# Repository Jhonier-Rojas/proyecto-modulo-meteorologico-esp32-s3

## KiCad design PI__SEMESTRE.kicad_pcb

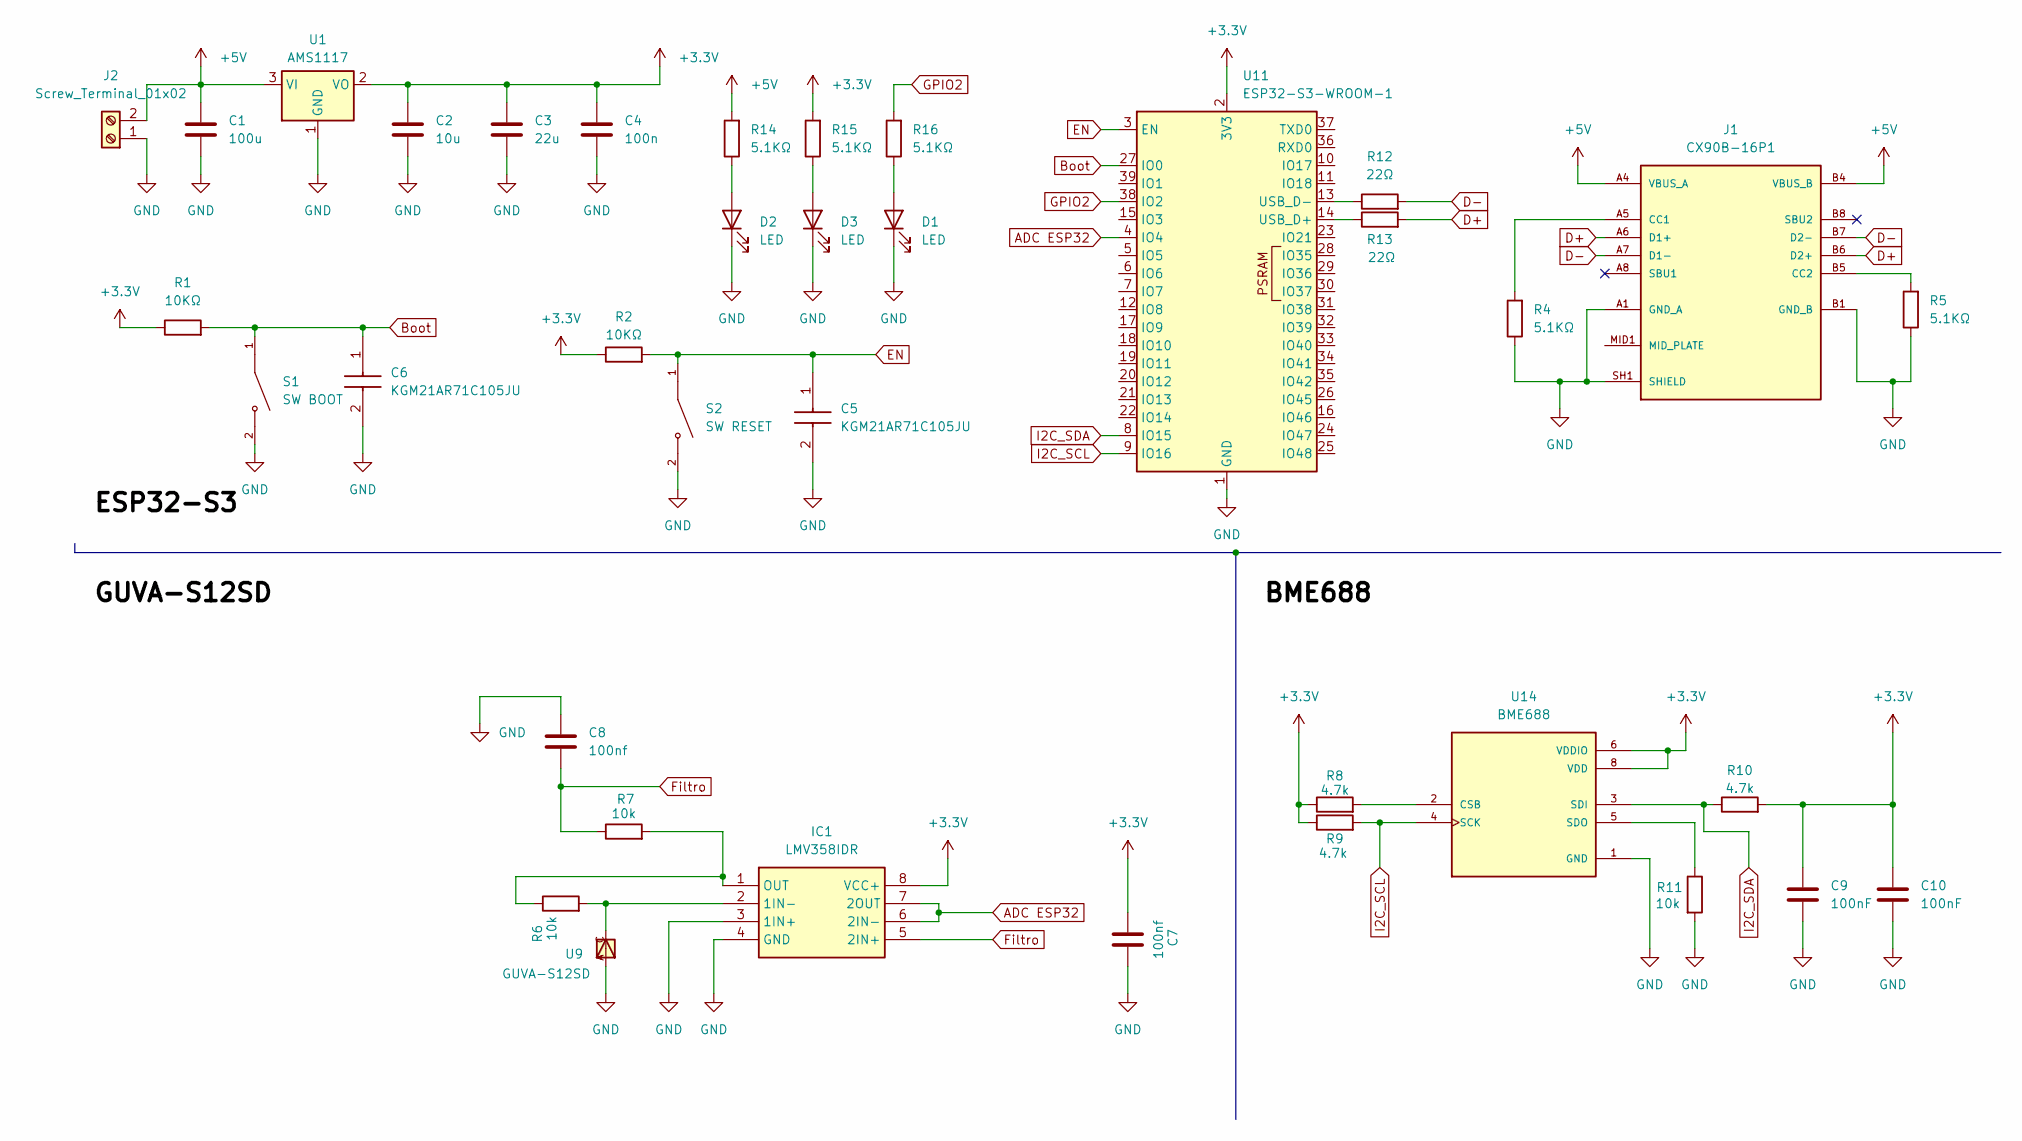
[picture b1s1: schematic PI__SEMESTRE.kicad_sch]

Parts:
C1: 100u; C_0805_2012Metric
C2: 10u; C_0805_2012Metric
C3: 22u; C_0805_2012Metric
C4: 100n; C_0805_2012Metric
C5, C6: KGM21AR71C105JU; CAPC2012X145N; Mouser Part Number 581-KGM21AR71C105JU
C7, C8: 100nf; C_0805_2012Metric
C9, C10: 100nF; C_0805_2012Metric
D1, D2, D3: LED; LED_1206_3216Metric
IC1: LMV358IDR; SOIC127P600X175-8N; Mouser Part Number 595-LMV358IDR
J1: CX90B-16P1; HIROSE_CX90B-16P1; PARTREV 23.04.05
J2: Screw_Terminal_01x02
R1, R2: 10KΩ; R_0805_2012Metric
R4, R5, R14, R15, R16: 5.1KΩ; R_0805_2012Metric
R6, R7, R11: 10k; R_0805_2012Metric
R8, R9, R10: 4.7k; R_0805_2012Metric
R12, R13: 22Ω; R_0805_2012Metric
S1: SW BOOT; SW_TS-1088-AR02016; PARTREV N/A
S2: SW RESET; SW_TS-1088-AR02016; PARTREV N/A
U1: AMS1117; SOT-223-3_TabPin2
U9: GUVA-S12SD; MPN GUVA-S12SD
U11: ESP32-S3-WROOM-1; XCVR_ESP32-S3-WROOM-1U-N16R8
U14: BME688; IC_BME688; PARTREV 1.0

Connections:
+3.3V: C2.1, C3.1, C4.1, C7.2, C9.1, C10.1, IC1.8 (VCC+), R1.1, R2.1, R8.1, R9.1, R10.2, R15.2, U1.2 (VO), U11.2 (3V3), U14.6 (VDDIO), U14.8 (VDD)
+5V: C1.1, J1.A4 (VBUS_A), J1.A9 (VBUS_A), J1.B4 (VBUS_B), J1.B9 (VBUS_B), J2.2, R14.2, U1.3 (VI)
ADC ESP32: IC1.6 (2IN-), IC1.7 (2OUT), U11.4 (IO4)
Boot: C6.1, R1.2, S1.1, U11.27 (IO0)
D+: J1.A6 (D1+), J1.B6 (D2+), R13.2
D-: J1.A7 (D1-), J1.B7 (D2-), R12.2
EN: C5.1, R2.2, S2.1, U11.3 (EN)
Filtro: C8.1, IC1.5 (2IN+), R7.1
GND: C1.2, C2.2, C3.2, C4.2, C5.2, C6.2, C7.1, C8.2, C9.2, C10.2, D1.1 (K), D2.1 (K), D3.1 (K), IC1.3 (1IN+), IC1.4 (GND), J1.A1 (GND_A), J1.A12 (GND_A), J1.B1 (GND_B), J1.B12 (GND_B), J1.SH1 (SHIELD), J1.SH2 (SHIELD), J1.SH3 (SHIELD), J1.SH4 (SHIELD), J1.SH5 (SHIELD), J1.SH6 (SHIELD), J2.1, R4.1, R5.1, R11.2, S1.2, S2.2, U1.1 (GND), U9.A, U11.1 (GND), U11.40 (GND), U11.41 (GND), U14.1 (GND), U14.7 (GND)
GPIO2: R16.2, U11.38 (IO2)
I2C_SCL: R9.2, U11.9 (IO16), U14.4 (SCK)
I2C_SDA: R10.1, U11.8 (IO15), U14.3 (SDI)
unnamed: D1.2 (A), R16.1
unnamed: D2.2 (A), R14.1
unnamed: D3.2 (A), R15.1
unnamed: IC1.2 (1IN-), R6.2, U9.C
unnamed: IC1.1 (OUT), R6.1, R7.2
unnamed: J1.A5 (CC1), R4.2
unnamed: J1.B5 (CC2), R5.2
unnamed: J1.MID1 (MID_PLATE), J1.MID2 (MID_PLATE)
unnamed: R13.1, U11.14 (USB_D+)
unnamed: R12.1, U11.13 (USB_D-)
unnamed: R8.2, U14.2 (CSB)
unnamed: R11.1, U14.5 (SDO)

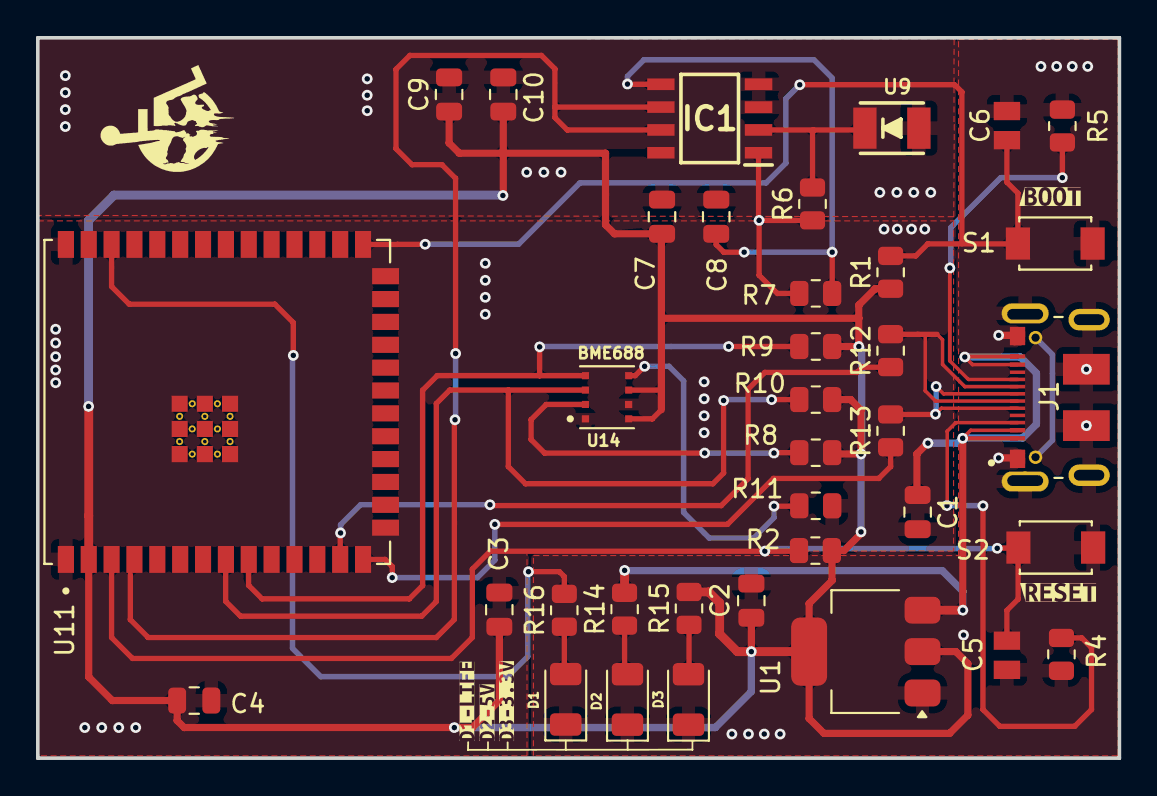
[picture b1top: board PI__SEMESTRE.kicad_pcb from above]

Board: 2 copper layers, 60.1 x 40.0 mm, 41 parts (0 on the bottom side), 24 nets.

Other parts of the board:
kibuzzard-6A0FC9A7: G***; kibuzzard-6A0FC9A7
kibuzzard-6A0FC9CC: G***; kibuzzard-6A0FC9CC
kibuzzard-6A0FC95D: G***; kibuzzard-6A0FC95D
kibuzzard-6A0FCD51: G***; kibuzzard-6A0FCD51
kibuzzard-6A0FCD67: G***; kibuzzard-6A0FCD67

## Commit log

2026-04-24 primer commit del proyecto kicad
2026-04-24 Unifico esquematicos y elimino hojas innecesarias
2026-04-26 cambios realizados para el esp32 s3 y unificacion de hojas
2026-04-26 Actualizo archivos KiCad
2026-04-26 se corrige el esquematico del BME688 que sugirio el profesor, se le colocan etiquetas a las conexiones al esp32.
2026-04-27 se realizo los cambios que el profesor indico en la parte del guva s12sd, corrigiendo pistas, separando componentes y agregando el seguidor de voltaje que va desde nuestro filtro paso bajo hasta la e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
2026-04-28 se implementan tanto huella y diseño 3D de los pulsadores booty reset, y tambien se le implementan la huella y diseño 3D a otros componentes como BME688, LMV358I, GUVA S12SD. se empieza a ordenar los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
2026-04-29 se empieza a realizar el diseño para la pcb se dejan los componentes pocisionados para luego hacer las pistas, se rellena el contorno de la placa con conexion GND.
2026-04-30 se colocan algunas pistas de potencia, se unifican las dos capas en una misma pcb se hace pruebas de tamaños
2026-05-01 Se deja ya lista la pcb para que el profesor pase revision y noos indique los errores a corregir
2026-05-04 algunas correcciones del profesor
2026-05-07 se hacen los cambios de las pistas esquineras de (90 Grados) a curvas de (45 Grados) estos cambios solamente se le hicieron a las pistas azules, se le agrega la conexion del led faltante del (ESP) pa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
2026-05-08 empece atrabajar las pistas rojas de la pcb
2026-05-08 ignorar
2026-05-11 Se corrigió el tamaño de algunas pistas y también se ajustaron las curvas en las esquinas, con el fin de evitar terminaciones en punta. De esta manera, las pistas quedan con un trazado más limpio, un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
2026-05-11 se termino de verificar las pistas, su anchor y se corrigió la curva de las pistas
2026-05-11 se corrigen las pistas del usb-c, se corrigen las pistas azules a rectas a 45 grados.
2026-05-11 se realizo la correcion del anchor de las pistas y en lo posible quedaran a 45 grados
2026-05-11 se corrigio anchor de unas pistas y su angulo a 45 grados
2026-05-11 se corrigio el angulo y el ancho de las pistas que faltaban
2026-05-12 se corrigen direcciones, curvas y tamaños de pistas
2026-05-15 se hicieron los cambios posibles que sugirio el docente, se cambiaron pistas a 45 grados se elimino los valores de los condensadores y resistencias, se hizo tambien el cambio proctecion contra ruido 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
2026-05-19 se actualizo la serigrafia en la pcb
2026-05-21 se organizo el tamaño de las pistas
2026-05-22 se corrigieron muchoss errores tanto que al diseño pcb le hacian falta 4 capacitores porque no tenian huella suministrada, se hicieron cambios de serigrafia, se acomodaron algunos errores tanto de la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
2026-05-22 fix: se solucionan algunos errores de clearance y planos de tierra
2026-05-22 se voltean las resistencias de la cara de abajo
2026-05-23 se corrigieron los condensadores que estaban en la parte de atraas de la placa
2026-05-23 se corrigio lo que sugerio el docente, pasando los componentes que estaban en la parte de atras de la placa
2026-05-23 se agrega nuestro logo se hacen las ultimos cambios para mandar hacer la pcb
2026-05-23 ing pruebas de fabricacion
2026-05-23 se hicieroon cambios pequeños
2026-05-23 se eliminaron componentes demas
